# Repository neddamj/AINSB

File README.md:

# AINSB - AI Navigation System for the Blind
The aim of this project is to develop a prototype device that helps to enable safe navigation for the blind/visually impaired in various environments. This is a research project done in partial fulfillment of the BSc. Electronics Engineering at UWI Mona.

## Project Overview
According to the project requirements, the primary objectives of the project are to:
* Identify various objects in the path of the user
* Estimate the distance of those objects from the user
* Provide auditory and/or tactile feedback to direct the user

The secondary/stretch objectives include:
* Apply face recognition to identify persons familiar to the user of the device 
* Accept voice commands from the user 

As such, the software implementation of the project up to this point has been divided into the following section:
* Face Recognition
* Depth Estimation
* Object Detection
* Text to Speech
* Tactile Feedback

Each of the previously mentioned sections contain the code and files that were used during the R&D process for each of those tasks, and all code can be found in the src folder.

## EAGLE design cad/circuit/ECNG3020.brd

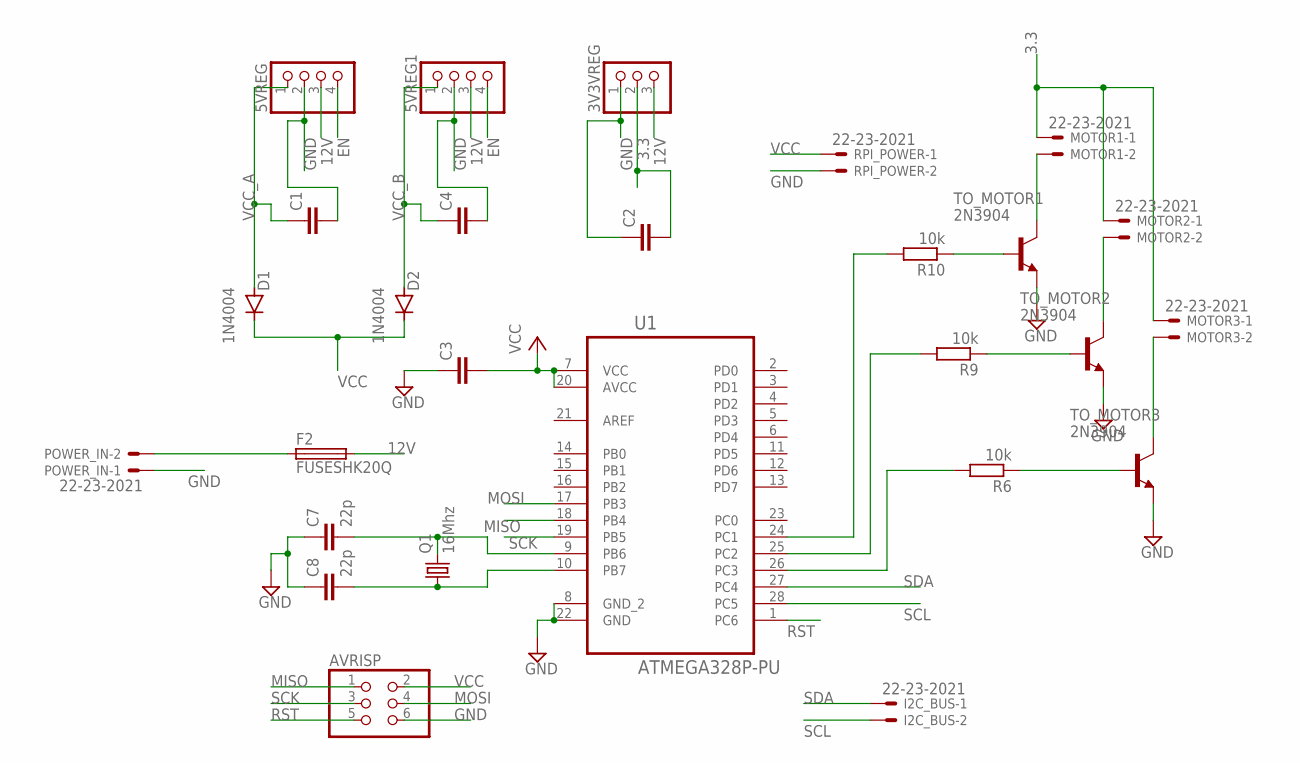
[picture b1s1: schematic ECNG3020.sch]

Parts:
3V3VREG: PINHD-1X3M; 1X03M
5VREG, 5VREG1: PINHD-1X4M; 1X04M
AVRISP: PINHD-2X3; 2X03
C1, C2, C3, C4: C2,5-3; C2.5-3
C7, C8: 22p; C050-024X044
D1, D2: 1N4004; DO41-10
F2: FUSESHK20Q; SHK20Q
I2C_BUS: 22-23-2021
MOTOR1, MOTOR2, MOTOR3: 22-23-2021
POWER_IN: 22-23-2021
Q1: 16Mhz; HC49/S
R6, R9, R10: 10k; 0207/10
RPI_POWER: 22-23-2021
TO_MOTOR1, TO_MOTOR2, TO_MOTOR3: 2N3904; TO92
U1: ATMEGA328P-PU; DIP254P762X457-28

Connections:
3.3: 3V3VREG.2, C2.2, MOTOR1.1, MOTOR2.1, MOTOR3.1
12V: 3V3VREG.3, 5VREG.3, 5VREG1.3, F2.2A (2)
EN: 5VREG.4, 5VREG1.4
GND: 3V3VREG.1, 5VREG.2, 5VREG1.2, AVRISP.6, C1.2, C2.1, C3.1, C4.2, C7.1, C8.1, POWER_IN.1, RPI_POWER.2, TO_MOTOR1.3 (E), TO_MOTOR2.3 (E), TO_MOTOR3.3 (E), U1.8 (GND_2), U1.22 (GND)
MISO: AVRISP.1, U1.18 (PB4)
MOSI: AVRISP.4, U1.17 (PB3)
unnamed: R10.2, U1.24 (PC1)
unnamed: R9.2, U1.25 (PC2)
unnamed: C7.2, Q1.2, U1.9 (PB6)
unnamed: R6.2, U1.26 (PC3)
unnamed: C8.2, Q1.1, U1.10 (PB7)
unnamed: R10.1, TO_MOTOR1.2 (B)
unnamed: MOTOR3.2, TO_MOTOR3.1 (C)
unnamed: MOTOR2.2, TO_MOTOR2.1 (C)
unnamed: MOTOR1.2, TO_MOTOR1.1 (C)
unnamed: F2.1A (1), POWER_IN.2
unnamed: R9.1, TO_MOTOR2.2 (B)
unnamed: R6.1, TO_MOTOR3.2 (B)
RST: AVRISP.5, U1.1 (PC6)
SCK: AVRISP.3, U1.19 (PB5)
SCL: I2C_BUS.2, U1.28 (PC5)
SDA: I2C_BUS.1, U1.27 (PC4)
VCC: AVRISP.2, C3.2, D1.C, D2.C, RPI_POWER.1, U1.7 (VCC), U1.20 (AVCC)
VCC_A: 5VREG.1, C1.1, D1.A
VCC_B: 5VREG1.1, C4.1, D2.A

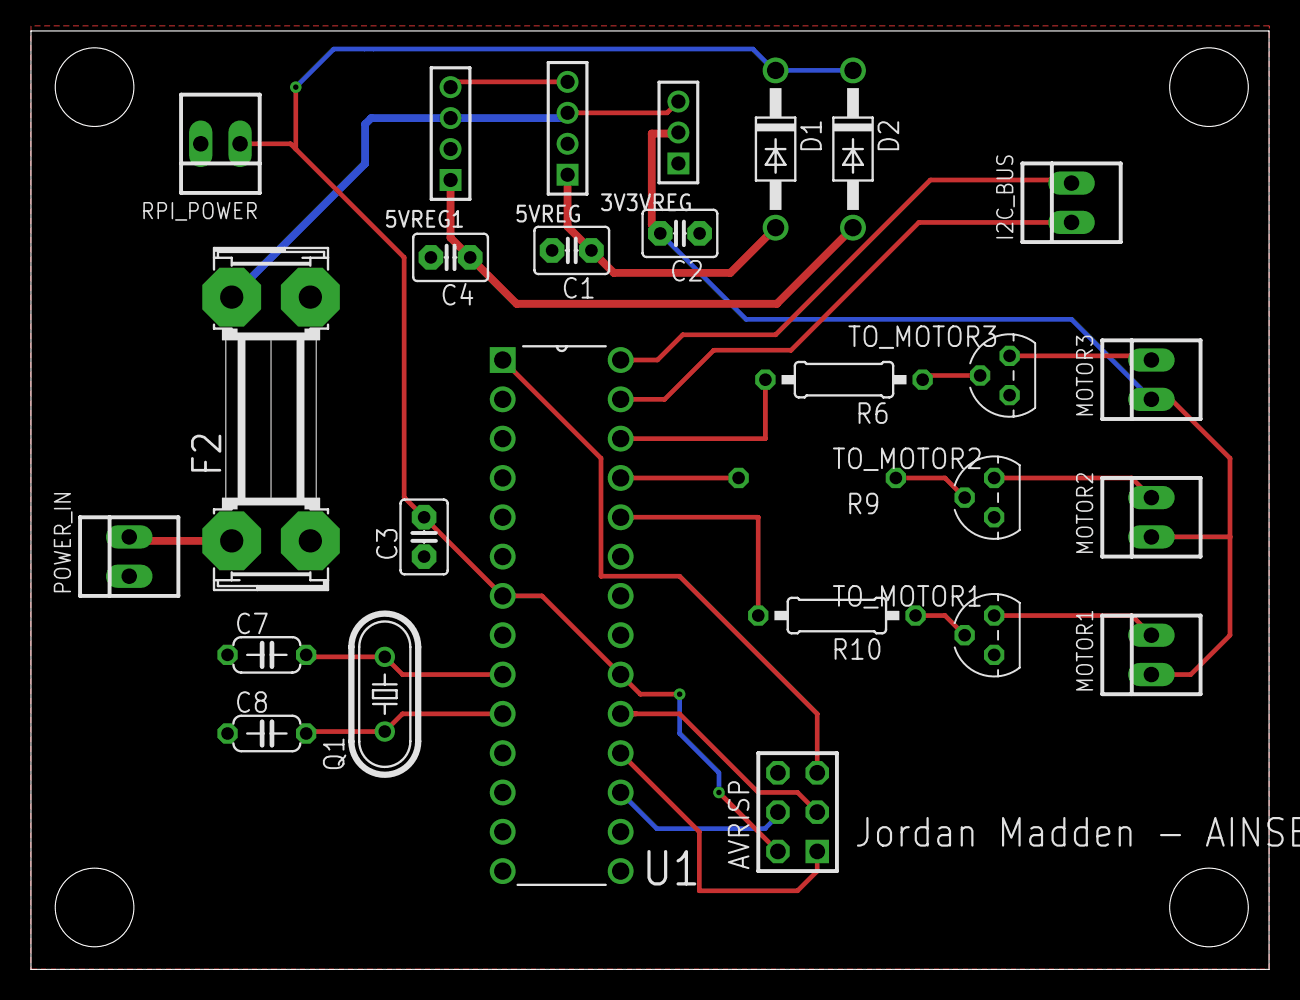
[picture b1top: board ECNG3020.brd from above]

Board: 2 copper layers, 80.0 x 60.6 mm, 27 parts (1 on the bottom side), 25 nets.

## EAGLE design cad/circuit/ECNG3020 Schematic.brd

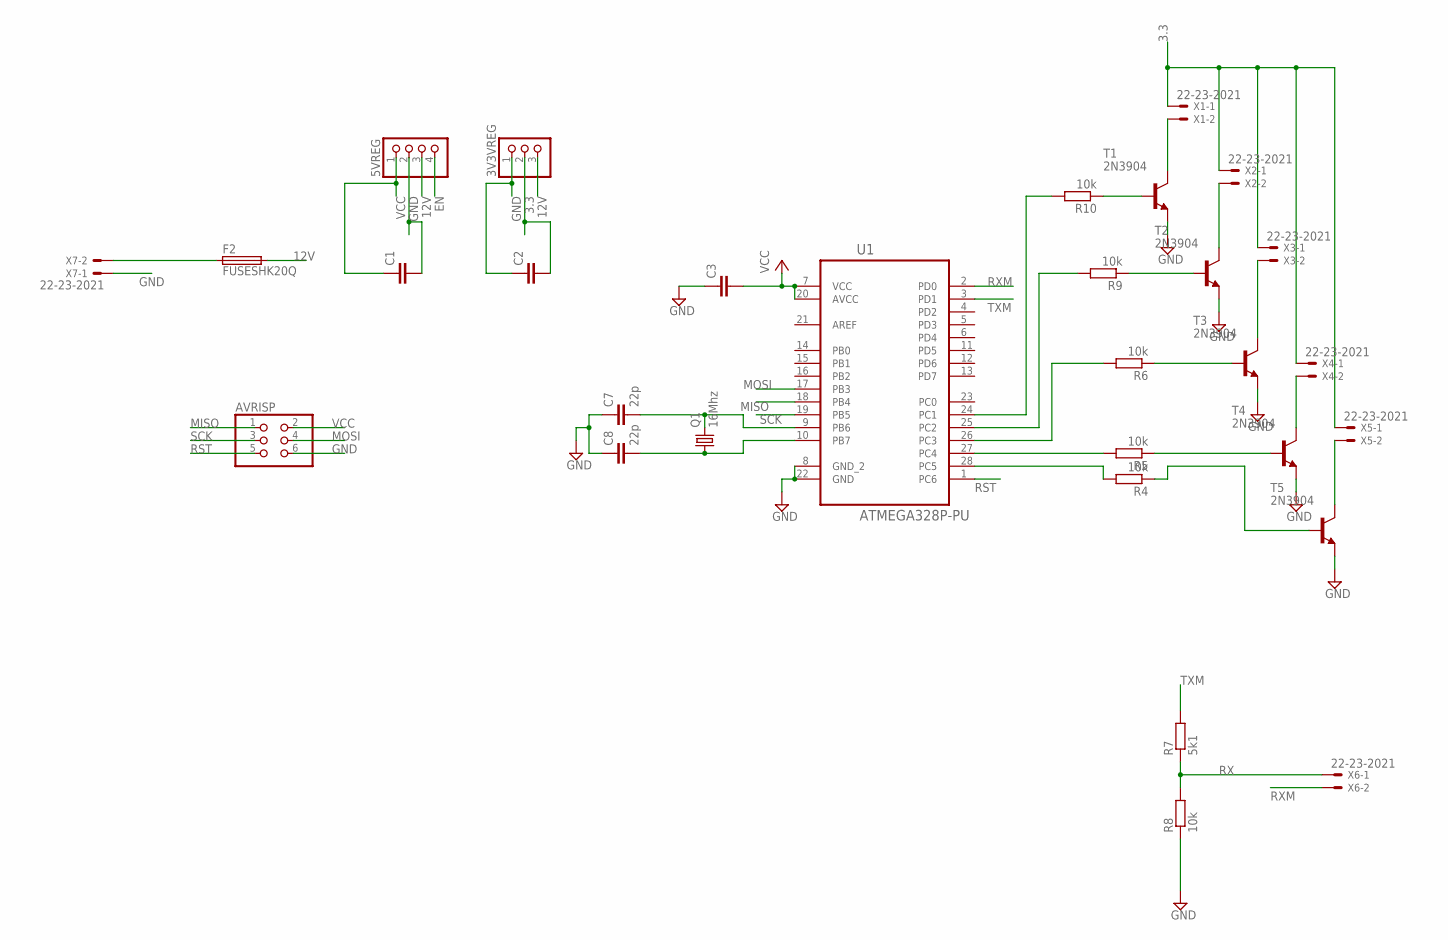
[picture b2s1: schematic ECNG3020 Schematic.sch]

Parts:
3V3VREG: PINHD-1X3M; 1X03M
5VREG: PINHD-1X4M; 1X04M
AVRISP: PINHD-2X3; 2X03
C1, C2, C3: C2,5-3; C2.5-3
C7, C8: 22p; C050-024X044
F2: FUSESHK20Q; SHK20Q
Q1: 16Mhz; HC49/S
R4, R5, R6, R8, R9, R10: 10k; 0207/10
R7: 5k1; 0207/10
T1, T2, T3, T4, T5: 2N3904; TO92
U1: ATMEGA328P-PU; DIP254P762X457-28
X1, X2, X3, X4, X5, X6, X7: 22-23-2021

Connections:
3.3: 3V3VREG.2, C2.2, X1.1, X2.1, X3.1, X4.1, X5.1
12V: 3V3VREG.3, 5VREG.3, F2.2A (2)
EN: 5VREG.4
GND: 3V3VREG.1, 5VREG.2, AVRISP.6, C1.2, C2.1, C3.1, C7.1, C8.1, R8.1, T1.3 (E), T2.3 (E), T3.3 (E), T4.3 (E), T5.3 (E), U1.8 (GND_2), U1.22 (GND), X7.1
MISO: AVRISP.1, U1.18 (PB4)
MOSI: AVRISP.4, U1.17 (PB3)
unnamed: R10.2, U1.24 (PC1)
unnamed: R9.2, U1.25 (PC2)
unnamed: C7.2, Q1.2, U1.9 (PB6)
unnamed: R6.2, U1.26 (PC3)
unnamed: C8.2, Q1.1, U1.10 (PB7)
unnamed: R10.1, T1.2 (B)
unnamed: R4.1, T5.2 (B)
unnamed: T5.1 (C), X5.2
unnamed: T4.1 (C), X4.2
unnamed: T3.1 (C), X3.2
unnamed: T2.1 (C), X2.2
unnamed: T1.1 (C), X1.2
unnamed: F2.1A (1), X7.2
unnamed: R9.1, T2.2 (B)
unnamed: R6.1, T3.2 (B)
unnamed: R5.1, T4.2 (B)
unnamed: R5.2, U1.27 (PC4)
unnamed: R4.2, U1.28 (PC5)
RST: AVRISP.5, U1.1 (PC6)
RX: R7.1, R8.2, X6.1
RXM: U1.2 (PD0), X6.2
SCK: AVRISP.3, U1.19 (PB5)
TXM: R7.2, U1.3 (PD1)
VCC: 5VREG.1, AVRISP.2, C1.1, C3.2, U1.7 (VCC), U1.20 (AVCC)

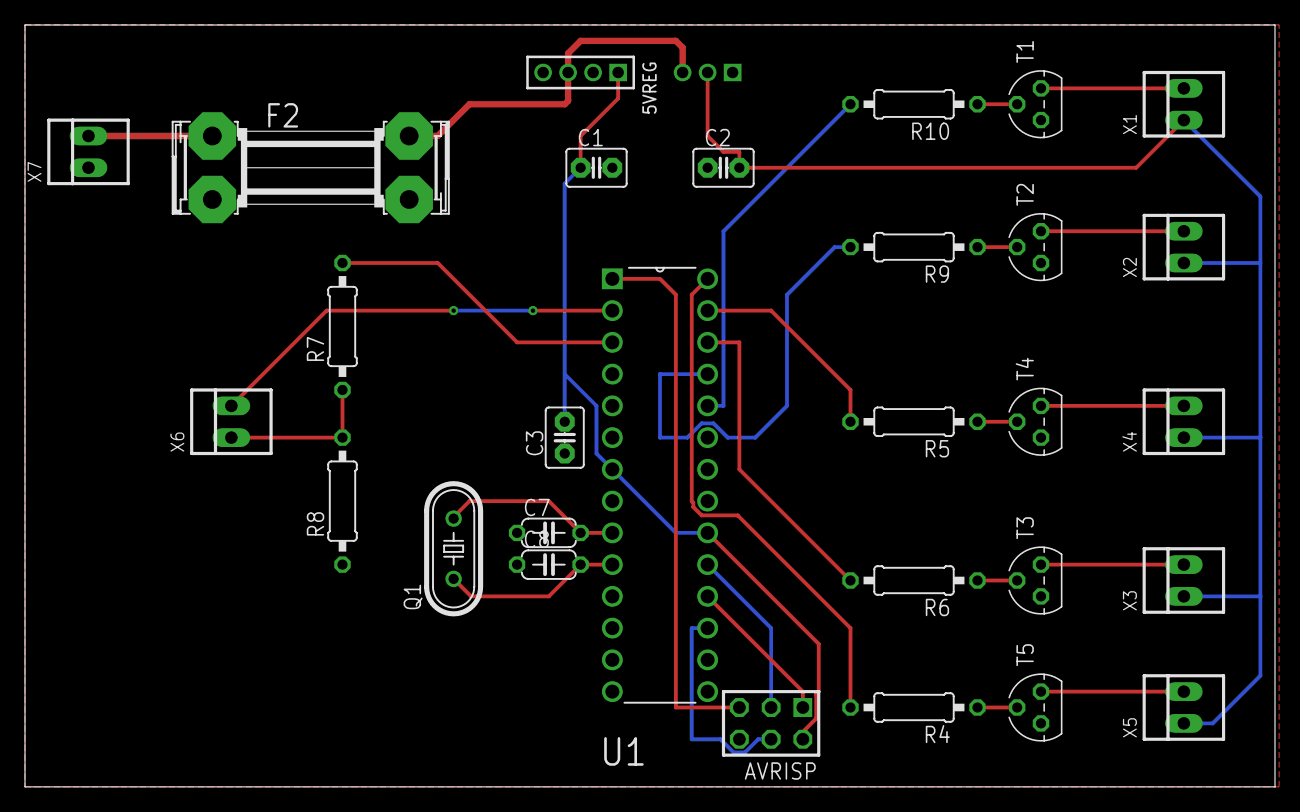
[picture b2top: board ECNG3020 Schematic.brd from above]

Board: 2 copper layers, 100.0 x 61.0 mm, 30 parts (1 on the bottom side), 29 nets.

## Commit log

2021-01-02 Google text to speech api
2021-01-02 yolov3
2021-01-02 Add gitignore
2021-01-02 TF2 object detection
2021-01-02 Face recognition
2021-01-02 Added gitignore
2021-01-04 Updated training script for face rec
2021-01-04 Attempting to optimize the YOLO object detection
2021-01-05 Testing optimizations
2021-01-05 Tested multiple models
2021-01-05 Code refractoring
2021-01-09 Modified the README
2021-01-09 Added a gitignore
2021-01-09 Renamed folder
2021-01-09 Optimized code for the raspberry pi
2021-01-09 Face recognition for pi
2021-01-09 Removed the need for command line args
2021-01-10 Starting the code to provide the user with tactile feedback
2021-01-10 Code for tactile feedback
2021-01-13 Update the readme and began depth estimation code
2021-01-14 Testing realsense camera
2021-01-14 Extract depth of a point from the frame
2021-01-14 Filter the distance values from the camera
2021-01-14 Fixed test code for realsense
2021-01-14 Changed the filename
2021-01-14 Improved the filter function
2021-01-14 Updating the code
2021-01-15 IC:/Users/jorda/anaconda3/Scripts/activate
2021-01-15 Testing object detection on realsense using TF2 OD API
2021-01-16 Testing the integration of the code
2021-01-16 TestC:/Users/jorda/anaconda3/Scripts/activate
2021-01-16 Updated test.py
2021-01-16 Used command line args to extend functionality
2021-01-16 Integrating depth visualization in test code
2021-01-18 Testing new object detection method
2021-01-18 Modularized the face detection
2021-01-18 Modularized the face recognition
2021-01-19 Added training and inference scripts for face detection
2021-01-19 Beginning the navigation testing
2021-01-21 C:/Users/jorda/anaconda3/Scripts/activate
2021-01-21 Update face rec training script
2021-01-23 Testing the command functionalities
2021-01-28 Library difference between windows and linux so cmd line arg was made to check for that
2021-01-28 Updated files
2021-01-29 Testing rpi with TF2 OD API
2021-01-30 Ran object detection on rpi
2021-01-30 Updating the tactile feedback code
2021-01-30 Commented the rpi_test better
2021-01-30 Fix the filter distance function
2021-01-30 Update tactile feedback code
2021-01-30 Updated the test scripts
2021-01-30 Added shell scripts that help with installation of packages on raspberry pi
2021-01-31 Updated test
2021-02-01 Track the fps of the camera stream
2021-02-01 Threading the camera input and processing the data separately
2021-02-02 Testing the threading
2021-02-02 Wrote a class to read data from realsense camera on a separate thread
2021-02-02 Wrote a class that uses multithreading to read camera data
2021-02-02 Update code
2021-02-02 Threading the camera input in rpi_test.py
2021-02-03 Converting the model to tflite
2021-02-03 Testing TF Lite on raspberry pi
2021-02-03 Updating code
2021-02-03 Updating TF Lite test code
2021-02-03 Adding functionality to TF Lite test
2021-02-06 Added command functionality
2021-02-06 Removed path to labels
2021-02-06 Testing the navigation when no objects are detected
2021-02-08 Left and right commands
2021-02-09 Further navigation testing
2021-02-09 Navigation testing
2021-02-10 Updated rpi_test.py...havent tested it as yet
2021-02-14 I2C comm between rpi and arduino
2021-02-16 Using I2C instead of UART for comm
2021-02-17 Allowed the uC to execute commands based on received data from the pi
2021-02-17 Updated the PCB to use I2C instead of UART
2021-02-18 Sending nav commands from pi to arduino via I2C
2021-02-18 Received motion commands from pi via I2C
2021-02-22 Updated the schematic and board
2021-02-23 Added in rpi power source
2021-03-02 Testing conditions to make navigation more robust
2021-03-05 Made pcb smaller and added larger holes
2021-03-05 Made the hole sizes larger on pcb to fit screws
2021-03-10 Put 2 5V bucks in parallel to increase current to rpi
2021-03-16 Re-routed some connections
2021-03-16 Changed a navigation condition to allow for smoother navigation
2021-03-26 Fixed the output (to motors) functions
2021-03-26 Tested feedback with vibration motors
2021-03-26 Making the control smoother for better UX and ironing out bugs
2021-03-31 Made the cC:/Users/jorda/anaconda3/Scripts/activate
2021-03-31 Removed an import that wasnt necessary
2021-03-31 Tested and fixed the updates made so far
2021-04-02 made control predictions based on closest object to camera
2021-04-04 Update the main script
2021-04-21 Testing closest object based navigation and processing the other detections
2021-04-22 Tested and corrected code
2021-04-22 Audio playbck on RPI4
2021-04-22 Trying to improve the navigate algorithm
2021-04-24 Testing depth profiles
2021-04-24 Rename file and update depth filter
2021-04-26 Made depth profile function and updated requirements
2021-04-30 Added depth filter
2021-04-30 Rewriting navigation function
2021-04-30 Incorporating depth profile in navigation rewrite
2021-04-30 Made navigation heuristic-ish
2021-06-07 Test the vibration motors
2021-06-07 Updating requirements and gitignore
2021-06-12 Corrected 3.3V connection on PCB
2021-06-15 Adding filter_distance to realsense.py
2021-06-15 Moved filter_distance to realsense.py
2021-06-15 Labelling the depth profile graph
2021-06-15 Correcting syntax
2021-06-15 Update main to working code
2021-06-15 Bring main and rpi_test to the same version
2021-06-21 Getting results for paper
2021-06-22 Corrected a name in the imports
2021-06-22 Corrected out of bounds error
2021-06-22 Benchmarking speed of forward pass
2021-06-23 metric evaluation
2021-06-26 Organzing code
2021-06-28 Handling no detections
2021-06-30 Send command only when it differs from previous command
2021-06-30 Adding off function for haptics
2024-01-07 Created using Colaboratory
